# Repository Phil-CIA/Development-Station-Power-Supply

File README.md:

# Development-Station-Power-Supply

Integrated hardware and firmware repository for the development-station bench supply, its control electronics, front-panel display path, and supporting boards.

## What this repo actually contains

This is the active working repo for the full bench-supply platform, not just a single firmware target. It currently includes:

- ESP32 control firmware
- DSP regulator board design
- DSP regulator HAT / measurement-control board design
- original front-panel display board files
- USB hub board files and next-iter reference cleanup
- bring-up notes, pin maps, and display evaluation references

## Current direction (2026-08-14)

The project has shifted to a bring-up-first path.

**Recent progress:**
- Completed design simplification: migrated from adjustable 3-channel architecture to single +5V_Boot rail
- Connector contract verification passing (10 signal mappings validated across regulator↔HAT interface)
- Both RegulatorRevB and HAT-RevB boards electrically verified and ready for order prep

Current plan:
1. Use the hardware already built as the learning and validation baseline
2. Keep Rev-B bench work in proven bypass states while Rev-C electrical issues are closed
3. Complete Rev-C regulator and HAT design validation before PCB fabrication release
4. Continue front-panel work inside this repo
5. Evaluate two display paths in parallel:
   - the existing custom front-panel hardware already designed
   - the Elecrow CrowPanel Advance 4.3 inch HMI display
6. Avoid any new display redesign until bench results show it is needed

Current power-hardware status:

- The 3.3V regulator selector redesign is bench-proven in normal remote-sense operation; fallback and 5V TLV9352 checks remain open.
- The Rev-B HAT current-range switch remains bypassed pending MOSFET pinout and Vgs validation.
- HAT Rev-C implements four-channel differential OCP with dual INA2180A2 amplifiers and dual TLV1702 comparators.
- HAT Rev-C's 2026-08-14 clean ERC is superseded: a 2026-09-21 check found 82 ERC violations and 161 DRC violations plus 129 unconnected items (see RB-012). RB-012 remains a PCB release gate for Kelvin routing, bypassing, thresholds, hysteresis, footprints, and final DRC/connectivity validation.
- **Rev-D HAT is a hardware-first deliverable:** bare STM32F405RG LQFP64 plus the actual Teyleten Robot ESP32-C3 SuperMini are selected. The October 15 decisions in [#126](https://github.com/Phil-CIA/Development-Station-Power-Supply/issues/126) select native F405 USB CDC replacing CH340, a separate custom F405 loader over UART4 (PC10 TX to C3 GPIO0 RX; PC11 RX from GPIO1 TX), and independent ST-Link recovery. They supersede the October 13-14 USB-deferred/bare-MINI-1U proposals. The user's manually maintained `My_Edits` schematic must be preserved and reviewed; this worktree does not contain it and the repository's partial starter is not a substitute. Firmware pin alignment, electrical/footprint qualification, PCB/DRC, and bench validation remain open under #126; existing-indicator policy is [#125](https://github.com/Phil-CIA/Development-Station-Power-Supply/issues/125). See `docs/HAT_CONTROLLER_EVALUATION.md` for the reconciliation and historical review boundary. No fabrication or hardware validation is claimed.
- See `docs/DEV_STATION_HANDOFF_2026-08-14.md` for the active restart state.

**Immediate firmware priority (2026-10-24):** The next controller work is the
Rev-D STM32F405 transition. Do not spend bench time validating the compact F103
profile or continue optimizing F103 flash usage for future features. The F405
build already enables the full bring-up command set; its existing build is not
evidence of hardware compatibility or bench validation. Reconcile firmware
against the actual Rev-D hardware and re-verify behavior when that hardware is
available. See `docs/FIRMWARE_DEVELOPMENT_PLAN.md` and issue #126.

## Hardware scope in this repo

- External supply 12V feeds the regulator and HAT control stack
- Regulator board generates the main rails (+5V, +3.3V primary; +12V intermediate)
- HAT board handles measurement, feedback, and control behavior
- Front-panel display path is now treated as a system integration problem, not a redesign-first task
- USB hub files are retained as reference and redesign starting point where needed

## Hardware board status

**DSP-Regulator-RevB:** Ready for order
- ERC: 0 electrical errors (8 library warnings, non-critical)
- Connector contract: Verified against HAT-RevB (all 10 required signal mappings present)
- Latest netlist export: 2026-06-11 01:43:33

**DSP-Regulator-HAT-RevB:** Ready for order
- ERC: Clean (0 errors, 0 warnings)
- Connector contract: Verified with Regulator-RevB (all 10 required signal mappings present)
- Latest netlist export: 2026-06-11 01:10:51
- Design: Single +5V_Boot rail (simplified from adjustable 3-channel architecture)

These Rev-B files remain the built/bench baseline. Active redesign work now lives in the corresponding Rev-C project folders; do not release Rev-C fabrication outputs until its tracker gates are closed.

## Firmware status

Current firmware work in this repo includes:

- logical rail telemetry mapping
- automatic range selection support
- per-rail calibration and persistent configuration storage
- current-limit operating modes
- TFT front-panel support hooks

The active [CrowPanel UI plan](docs/display-project/crowpanel-screens-tracker.md)
adapts FNIRSI DPS-150 / IPS3608 styling to fixed +5V/+3.3V rails with editable
current limits and shared output control. It includes the issue/PR sequence
and VS Code Copilot session prompts; definitive CV/CC indication remains
gated on hardware validation.

## Current bench priorities

- Complete DRC checks and generate fabrication outputs for RegulatorRevB and HAT-RevB
- Place orders for both boards
- Safe first power-up and validation of the new boards
- Confirm regulator and HAT behavior on the bench
- Resume front-panel display bring-up
- Map the existing front-panel connector to the smart-display interface as needed

## Useful project references

- docs/SYSTEM_DEVELOPMENT_WORKFLOW.md — branch/PR workflow now in effect
- docs/FIRMWARE_DEVELOPMENT_PLAN.md — firmware feature inventory and milestone/branch plan
- docs/FAN_CONTROL_DEFINITION.md — issue #28 enclosure fan-control behavior spec (draft; tach path pending #29)
- docs/display-project/README.md
- docs/GPIO_PINOUT.md
- docs/USB_HUB_CHANGE_TRACKER.md
- docs/datasheets/README.md — local datasheet library; search with `python scripts/datasheet.py find <part>` before fetching

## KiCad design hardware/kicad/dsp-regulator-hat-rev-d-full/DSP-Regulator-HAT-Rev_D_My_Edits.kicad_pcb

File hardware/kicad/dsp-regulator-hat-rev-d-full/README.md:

# DSP Regulator HAT Rev-D Full - Selected-source integration

**Status: partial integration, not a complete full-HAT schematic.** The
editable HAT sheet was rebuilt on 2026-10-10 from the user's explicitly
selected Rev-C schematic. The design is not a fabrication release or a
bench-validated hardware identity; there is no PCB or PCB DRC result.

## Open and edit this project

- `DSP-Regulator-HAT-RevD-Full.kicad_pro` - project setup
- `DSP-Regulator-HAT-RevD-Full.kicad_sch` - root schematic
- `MCU.kicad_sch` - local hierarchical F405 support sheet
- `HAT.kicad_sch` - HAT circuits rebuilt from the selected Rev-C source
- `build_kicad/` - gitignored KiCad reports and exports

Open the `.kicad_pro` in KiCad 10.0.5. The root, MCU and HAT pages are
hierarchical pages 1, 2 and 3. The existing root schematic and MCU sheet were
left byte-identical. The reviewed support-only project in
`../dsp-regulator-hat-rev-d/` and the Rev-C projects remain separate and
unchanged.

## Selected HAT source

The user selected this exact file as the Rev-D HAT reuse baseline (the
2026-09-21 file):

`C:\Users\forch\OneDrive\JLCPCB files\Development station supply\Regulator Hat\REV C\KiCad Files\DSP-Regulator-HAT-RevC.kicad_sch`

Its SHA-256 is
`34EB41BA12237268CF8E8C640CFA2B76A4710CFF8DE99C9E988C9717D22872B3`.
A fresh KiCad CLI 10.0.5 netlist export contains **57 components and 83
nets**. This is a design-source selection only; it does not establish that
the schematic matches the supplied 2026-08-28 production PCB/Gerbers or any
physical board.

The earlier PR #112 pass used the repository Rev-C schematic (64 components,
105 nets). That source choice and its 0-error / 80-warning ERC result are
superseded and are not current validation evidence.

## HAT rebuild and interface mapping

The rebuilt HAT retains 55 of the selected source's 57 components. The old
Blue Pill U11 and ESP32-C3 development board U2, their no-connects, and
controller-only dangling labels/stubs were removed. No bare C3 module was
added. HAT references R1, R2 and R3 were renamed to R20, R21 and R22 because
the original references collide with the unchanged MCU sheet; their source
values and footprints are unchanged.

Existing F405 global labels were inspected before mapping. The supported
source paths are:

| F405 global interface | F405 pins | Selected-source HAT endpoints |
|---|---|---|
| `SPI_SCK`, `SPI_MISO`, `SPI_MOSI`, `Memory_CS` | PA5, PA6, PA7, PA8 | U12 W25Q128 |
| `UART1_TX`, `UART1_RX` | PB6, PB7 | U16 CH340C |
| `DISP_UART_TX`, `DISP_UART_RX` | PB10, PB11 | R77/R79 and J9 UDI |
| `I²C SCL_0`, `I²C SDA_0` | PB8, PB9 | J10 and U13 AHT20 |
| `FAN_PWM` | PB5 | R63/Q9 fan circuit; all source PB5 labels were normalized to this F405 global name without changing connector pin connectivity |
| `SWDIO`, `SWCLK` | PA13, PA14 | J17 and TP7/TP8 |

Source interface label changes are limited to `SPI SCK` -> `SPI_SCK`,
`SWDCLK` -> `SWCLK`, and `PB5` -> `FAN_PWM`; the source `+3.3V Boot` rail
labels were joined to the MCU's `+3V3` domain. The source J12 connector pin
mapping and all retained source-component pin connectivity remain unchanged.
The legacy WS2812B D12 DIN is grounded because its old controller is removed
and it is not the frozen low-current F405 LED circuit. CH340C CTS/RTS are
explicitly no-connected because the F405 contract uses TX/RX only.

The fan circuit is retained exactly from the selected schematic: J7 is a
3-pin connector; JP1 selects the J7/D11 supply path between `+5V_Boot` and
`+12V`; J7.1 is on the Q9-switched D11 path; J7.3 is a `Fan_Tach` endpoint
pulled up through source R3 (renumbered R22, 10 kΩ), with no F405 tach input.
Source R64 remains 100 kΩ. No fan polarity, supply, connector, resistor value
or population change was made to match the repository copy or frozen pin
target. The fan remains unbench-tested.

## Explicitly absent / unresolved

- The selected source has no ISET signal destinations at J12; its J12 pins
  remain GND, `+5V_Boot`, `+3.3V Boot`, `+12V`, GND, GND. F405 PA0/PA1 have
  their existing local bias circuitry but are not connected to invented HAT
  endpoints.
- The selected source has no shift register or AW9523. PA4/PC4/PC13 and the
  corresponding functions remain unintegrated; no endpoints were imported
  from the repository-only schematic or inferred from PCB content.
- MCU J4 remains a logical C3 interface on the support sheet, not a bare
  ESP32-C3-MINI-1U module implementation. The selected-source HAT UART labels
  are not connected to J4. C3 module power/straps/recovery/RF remain later
  work.
- The fan's source 100 kΩ R64 does not meet the frozen 10 kΩ fan-gate target;
  it was not changed. The pin-contract and safe-state review is still open.
- Remaining isolated legacy connector labels and missing custom library
  definitions are visible ERC warnings, not integrated functions.

## Validation

KiCad CLI 10.0.5 exports the three-sheet project as **95 components and 107
nets**. The comparison against the selected source confirms all 55 retained
source component values/footprints and all **1,056 pairwise source-component
pin connections** are unchanged, except D12 DIN, which is intentionally
grounded. Reference mapping is R1/R2/R3 -> R20/R21/R22. The expected SPI
flash, CH340, UDI, I2C, fan-control and SWD data/clock interfaces were checked
against the actual F405 global labels and netlist. J12 connector pins and the
source fan topology were checked separately.

Full-severity ERC reports **0 errors / 64 warnings**: 28 footprint-library,
28 symbol-library, 3 symbol/library mismatch and 5 isolated-pin-label
warnings. The report is generated with `--severity-all`; no ERC exclusions
were added. The warnings expose missing local library tables and unresolved
single-ended legacy connector labels. ERC/netlist checks are not PCB DRC,
electrical qualification, physical-board correlation, fabrication approval
or bench validation.

The exact source file, the full-project root/MCU files, the support-only
project, both repository Rev-C projects and the external production folder
were hash-checked; only the intended full-project HAT sheet changed among
those KiCad design files. See
[`HAT_REVD_PIN_AND_SUPPORT_CONTRACT.md`](../../../docs/HAT_REVD_PIN_AND_SUPPORT_CONTRACT.md)
for current boundaries and remaining release gates.

Re-run from the repository root in PowerShell:

```powershell
$project = "hardware\kicad\dsp-regulator-hat-rev-d-full"
$kicad = "$env:LOCALAPPDATA\Programs\KiCad\10.0\bin\kicad-cli.exe"
& $kicad sch erc "$project\DSP-Regulator-HAT-RevD-Full.kicad_sch" `
  --output "$project\build_kicad\ERC.rpt" --format report --severity-all
& $kicad sch export netlist "$project\DSP-Regulator-HAT-RevD-Full.kicad_sch" `
  --output "$project\build_kicad\DSP-Regulator-HAT-RevD-Full.net" `
  --format kicadsexpr
```

## SuperMini review closeout (user-accepted baseline)

- User accepted directly soldered through-hole header mounting for
  `SuperMini_Review:Teyleten_ESP32_C3_SuperMini` with the saved geometry:
  2.54mm pitch, 15.00mm row spacing, aligned rows, 1.7mm copper / 1.0mm
  drill, existing numbering, and USB at negative Y.
- Saved footprint text was audited and KiCad opening was user-confirmed.
- Physical hole fit, body/USB envelope, installed height, and antenna
  clearance were not verified in this review and are retained as
  implementation caveats (not blockers for this user-requested closeout).
- U2 assignment and PCB integration were not performed.
- Project-local library and footprint paths:
  - `hardware/kicad/dsp-regulator-hat-rev-d-full/fp-lib-table`
  - `hardware/kicad/dsp-regulator-hat-rev-d-full/SuperMini_Review.pretty/Teyleten_ESP32_C3_SuperMini.kicad_mod`

## Rev-D source preservation status (2026-10-24 user-confirmed)

- Confirmed Rev-D source set in this workspace:
  - `DSP-Regulator-HAT-Rev_D_My_Edits.kicad_sch`
  - `DSP-Regulator-HAT-Rev_D_My_Edits.kicad_pro`
  - `DSP-Regulator-HAT-Rev_D_My_Edits.kicad_pcb`
- SHA-256 (full):
  - `DSP-Regulator-HAT-Rev_D_My_Edits.kicad_sch`
    `56DBB1829EC3D60BC174B423BB3C076FEBDE61CBA844A3334B06E9B805610F86`
  - `DSP-Regulator-HAT-Rev_D_My_Edits.kicad_pro`
    `70C6AB58C39FFBC618B4C45C720BD51EEC6F3F04F0216B5DFA340010E44D0D51`
  - `DSP-Regulator-HAT-Rev_D_My_Edits.kicad_pcb`
    `8F7872B7946E3F1403190E5051BBDE5EB1976761201A710C185F5A749642770A`
- Historical copies only (not current source authority): `.history/`, `_restore_backup_*`,
  `../recovery-snapshots/`, and `../rev-d-source-staging/`.
- Current `DSP-Regulator-HAT-Rev_D_My_Edits.net`, `ERC.rpt`, and `DRC.rpt` files predate
  the current source timestamps and do not validate electrical correctness of this source set.

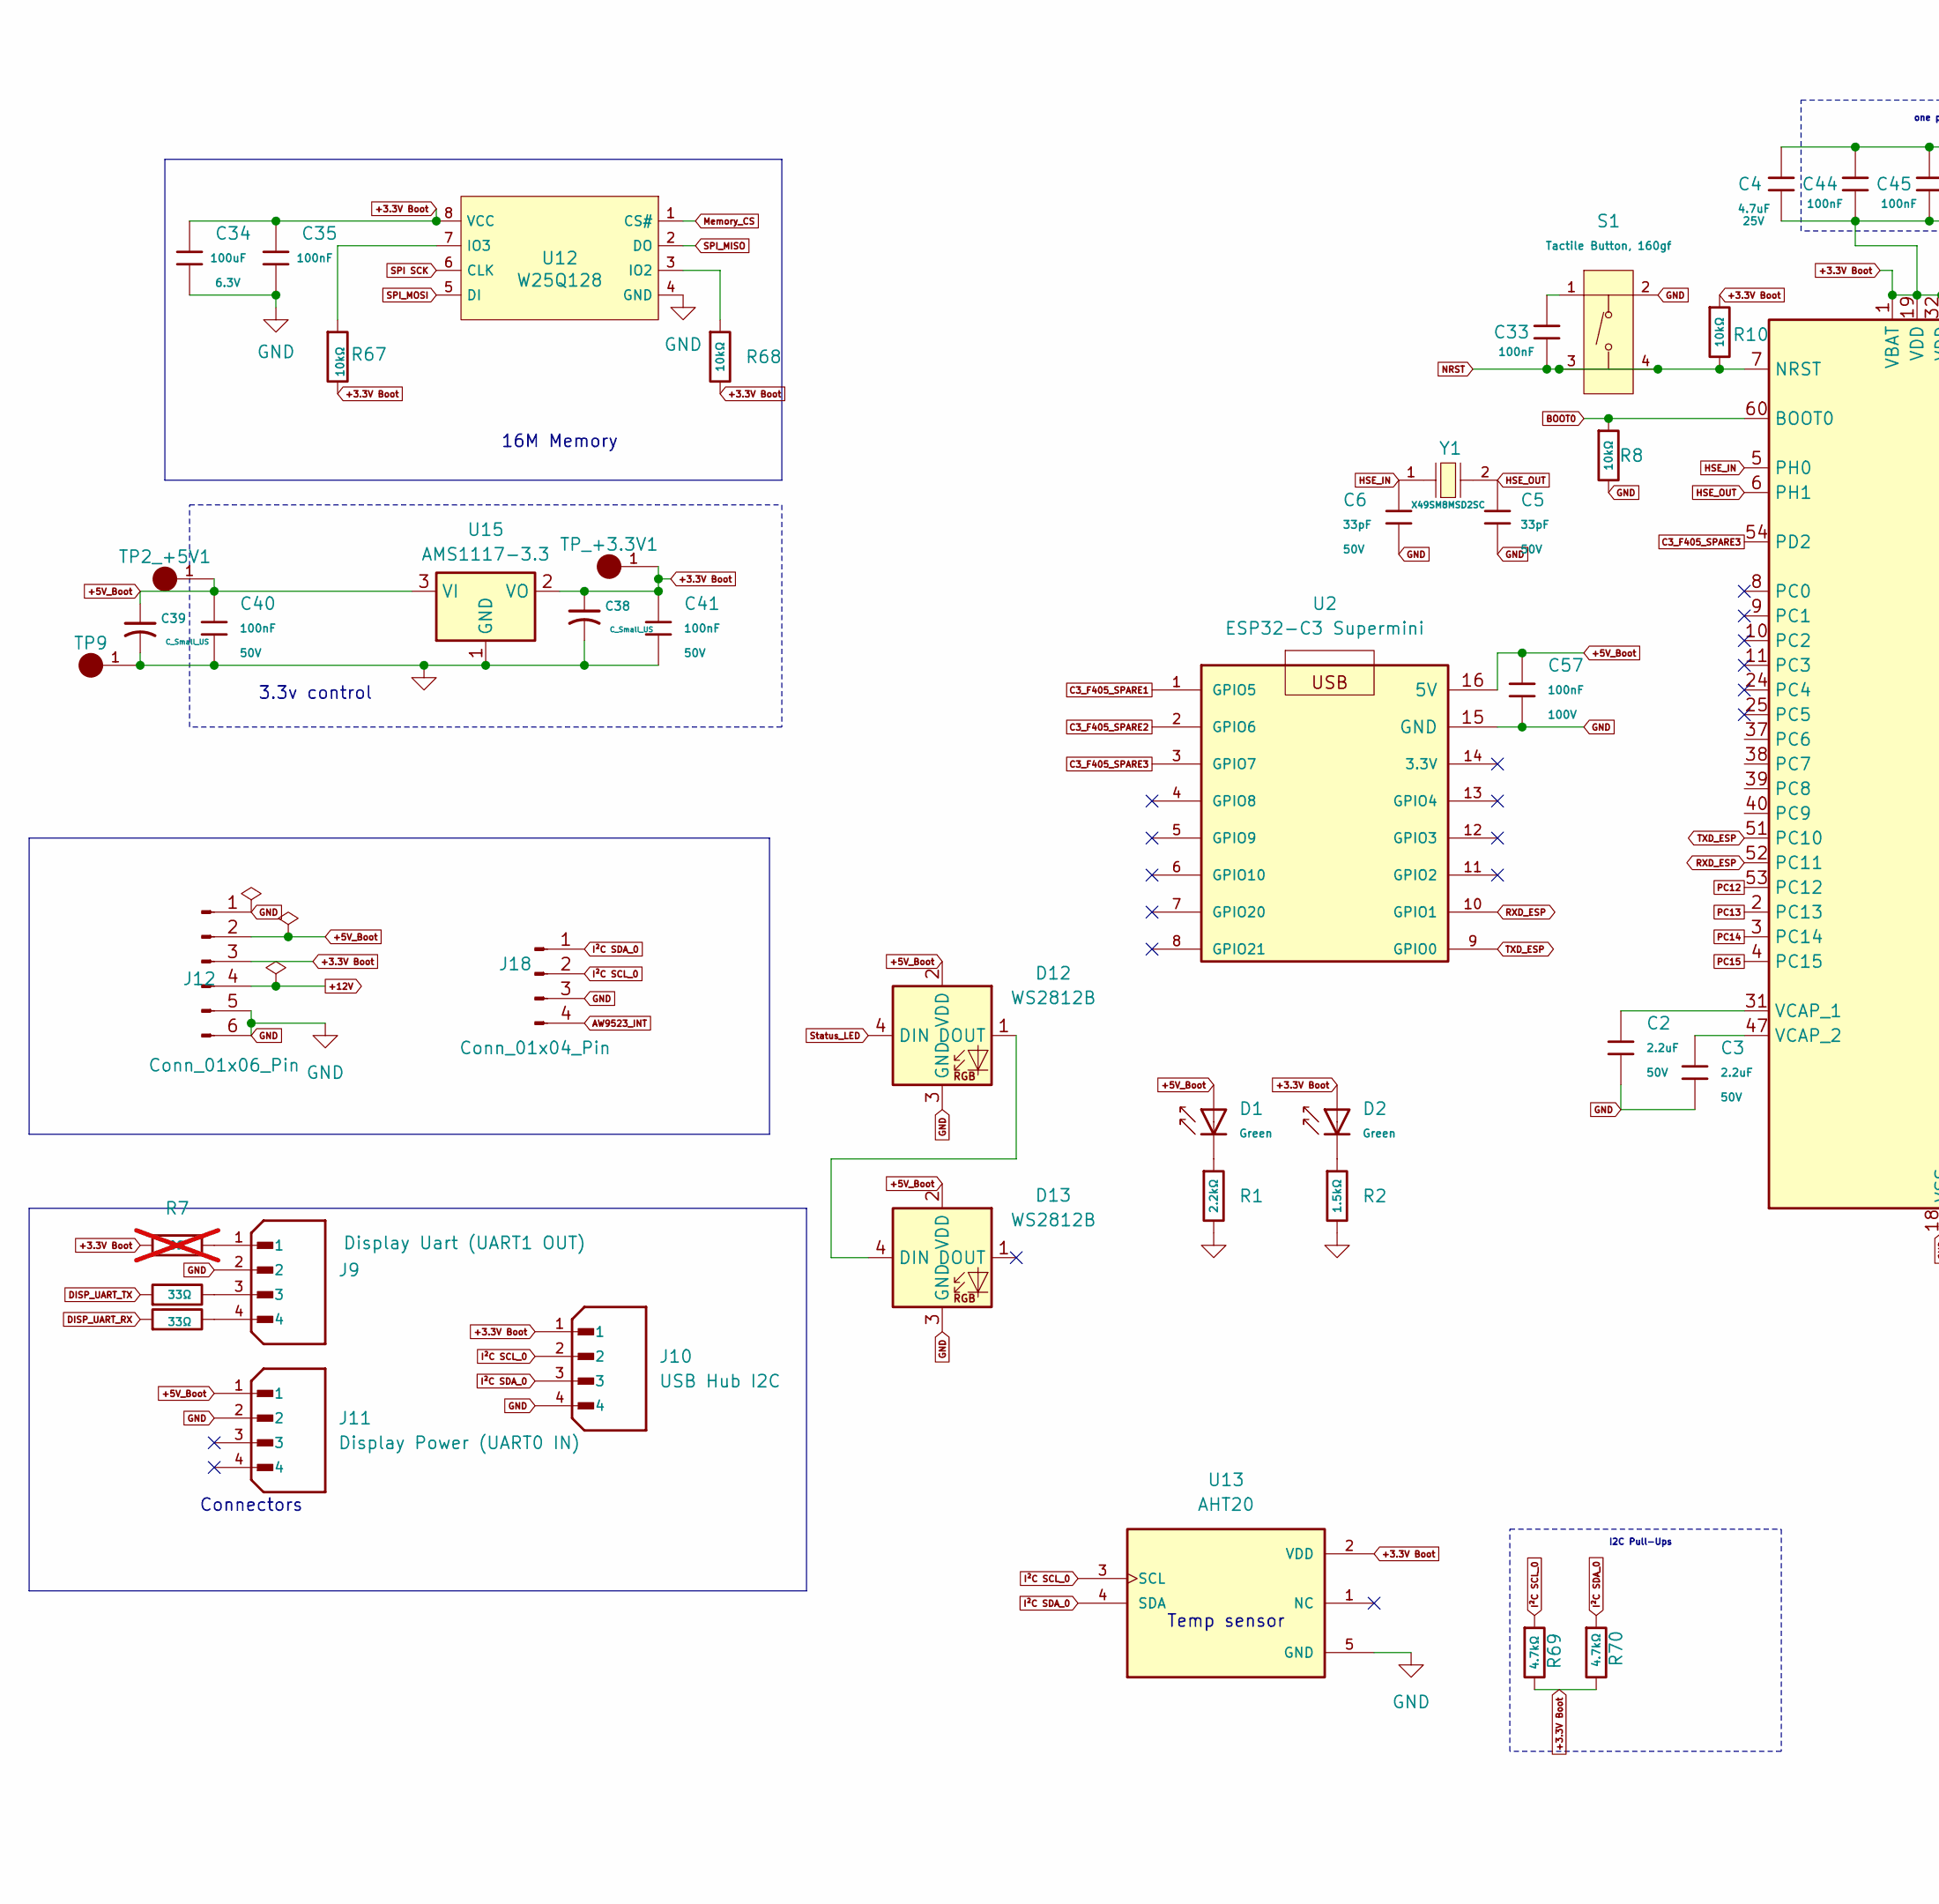
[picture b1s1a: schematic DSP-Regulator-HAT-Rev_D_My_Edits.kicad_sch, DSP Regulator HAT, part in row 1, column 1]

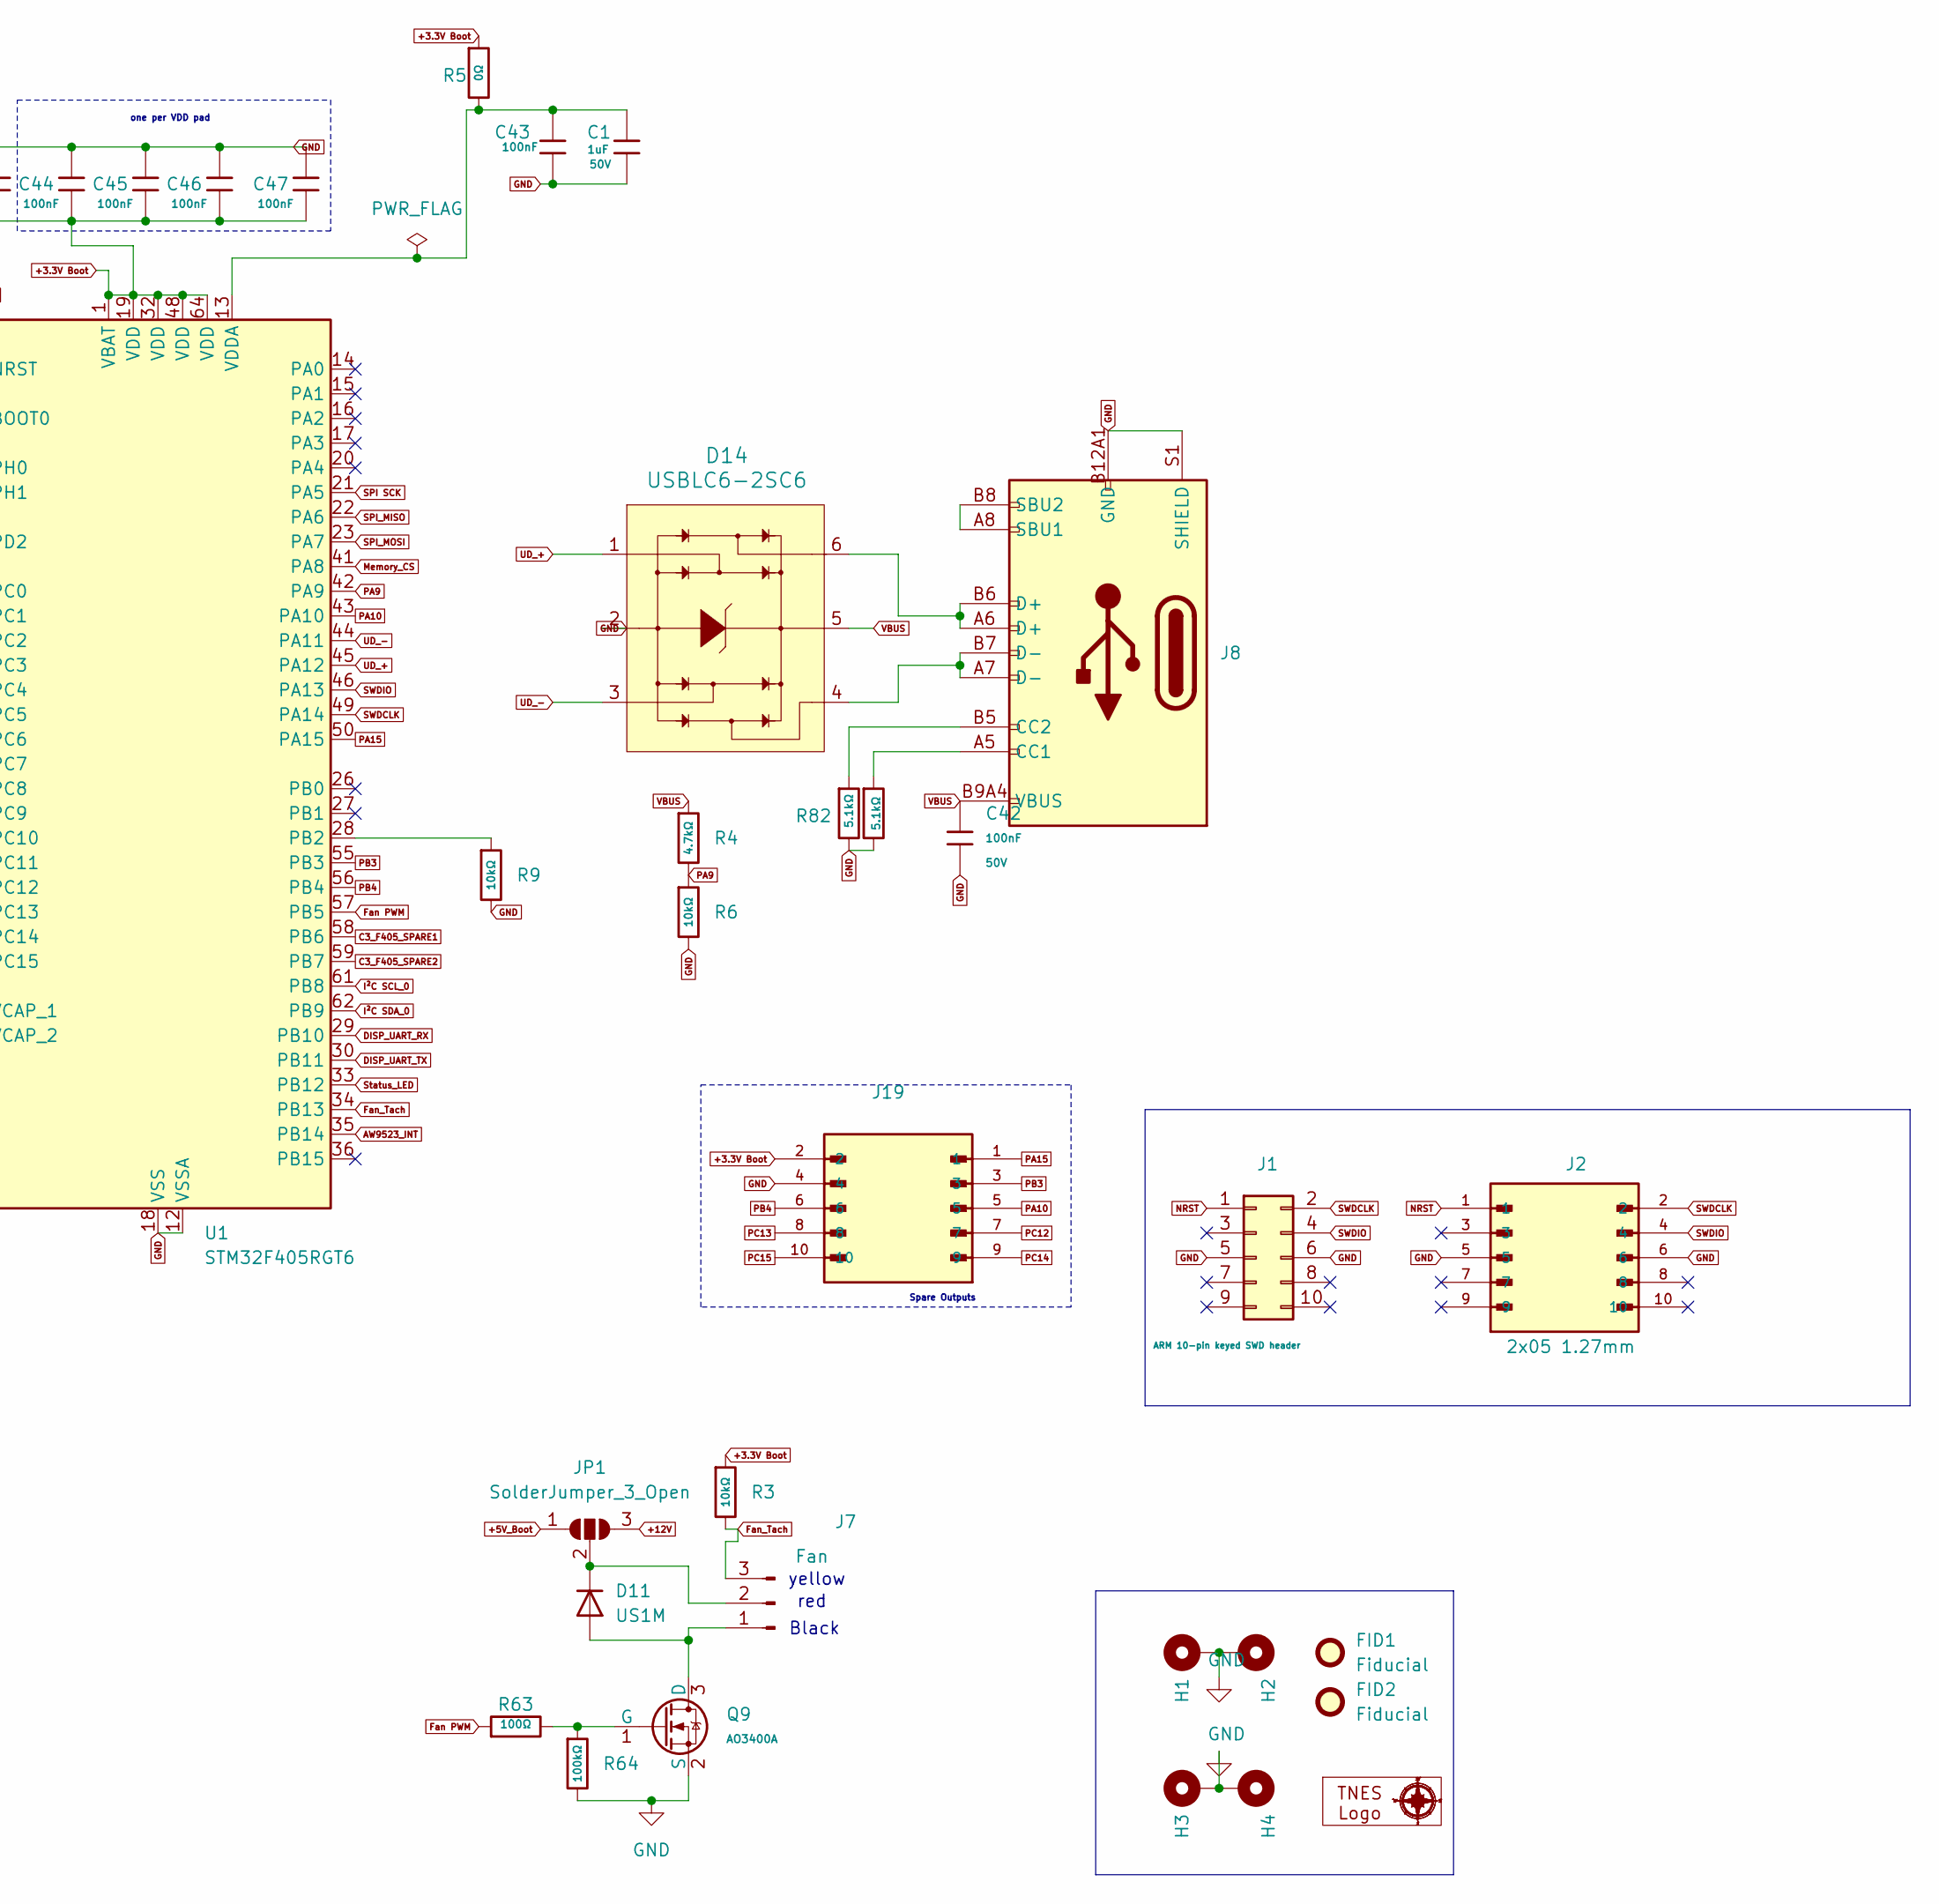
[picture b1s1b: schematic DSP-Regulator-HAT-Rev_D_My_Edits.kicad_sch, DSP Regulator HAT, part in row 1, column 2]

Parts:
5mm1: 5mm LOGO
C1: 1uF; C_0805; Voltage Rated 50V; Tolerance ±10%; Part CL21B105KBFNNNE; LCSC C28323
C2, C3: 2.2uF; C_0805; Voltage Rated 50V; Tolerance ±10%; Part CL21A225KBQNNNE; LCSC C377773
C4: 4.7uF; C_0805; Voltage Rated 25V; Tolerance ±10%; Part CL21A475KAQNNNE; LCSC C1779
C5, C6: 33pF; C_0805; Voltage Rated 50V; Tolerance ±5%; Part CC0805JRNPO9BN330; LCSC C107115
C33, C35, C40, C41, C42, C43, C44, C45, C46, C47: 100nF; C_0805; Voltage Rated 50V; Tolerance ±10%; Part CC0805KRX7R9BB104; LCSC C49678
C34: 100uF; C_1206; Voltage Rated 6.3V; Tolerance ±20%; Part CL31A107MQHNNNE; LCSC C15008
C38, C39: C_Small_US; CP_Elec_10x10; Part JVE25V470M10X10; LCSC C48615124
C57: 100nF; C_0805; Voltage Rated 100V; Tolerance ±10%; Part CL21B104KCFNNNE; LCSC C28233
D1, D2: Green; D_0805; Part KT-0805G; LCSC C2297
D11: US1M; D_SMA; LCSC C81191
D12, D13: WS2812B; LED-SMD_4P-L1.6-W1.5_XL-1615RGBC-WS2812B; LCSC C5349954
D14: USBLC6-2SC6; SOT23-6L; MPN USBLC6-2SC6; Digi-Key_PN 497-5235-1-ND
FID1, FID2: Fiducial; Fiducial_0.75mm_Mask1.5mm
H1, H2, H3, H4: MountingHole_Pad; MountingHole_3.5mm_Pad_Via
J1: ARM 10-pin keyed SWD header; IDC-Header_2x05_P2.54mm_Vertical
J2: 2x05 1.27mm; PinHeader_2x5_P1.27mm; PARTREV S
J7: Fan; PinHeader_1x03_P2.54mm_Vertical; LCSC C29275
J8: Connector, USB-TYPE-C-16P; TYPE-C-SMD_HX-TYPE-C-16PIN; LCSC C2927039
J9: Display Uart (UART1 OUT); JST_B4B-XH-A; PARTREV 7/4/21; LCSC C144395
J10: USB Hub I2C; JST_B4B-XH-A; PARTREV 7/4/21; LCSC C144395
J11: Display Power (UART0 IN); JST_B4B-XH-A; PARTREV 7/4/21; LCSC C144395
J12: Conn_01x06_Pin; PinHeader_1x06_P2.54mm_Vertical; LCSC C492414
J18: Conn_01x04_Pin; PinHeader_1x04_P2.54mm_Vertical; LCSC C492412
J19: 20021121-00010C4LF; PinHeader_2x5_P1.27mm; PARTREV S; LCSC C41376037
JP1: SolderJumper_3_Open; SolderJumper-3_P1.3mm_Open_RoundedPad1.0x1.5mm
Q9: AO3400A; Q_SOT-23; Part AO3400A; LCSC C20917
R1: 2.2kΩ; R_0805; Overload Voltage (Max) 150V; Tolerance ±1%; Part 0805W8F2201T5E; LCSC C17520
R2: 1.5kΩ; R_0805; Overload Voltage (Max) 150V; Tolerance ±1%; Part 0805W8F1501T5E; LCSC C4310
R3, R6, R8, R9, R10, R67, R68: 10kΩ; R_0805; Overload Voltage (Max) 150V; Tolerance ±1%; Part 0805W8F1002T5E; LCSC C17414
R4, R69, R70: 4.7kΩ; R_0805; Overload Voltage (Max) 150V; Tolerance ±1%; Part 0805W8F4701T5E; LCSC C17673
R5: 0Ω; R_0805; Overload Voltage (Max) 150V; Tolerance ±1%; Part 0805W8F0000T5E; LCSC C17477
R7: 0Ω; R_0805; Overload Voltage (Max) 150V; Tolerance ±1%; Part 0805W8F0000T5E; LCSC C17477; not fitted
R63: 100Ω; R_0805; Overload Voltage (Max) 150V; Tolerance ±1%; Part 0805W8F1000T5E; LCSC Part C105588
R64: 100kΩ; R_0805; Overload Voltage (Max) 150V; Tolerance ±1%; Part 0805W8F1003T5E; LCSC C149504
R77, R79: 33Ω; R_0805; Overload Voltage (Max) 150V; Tolerance ±1%; Part 0805W8F330JT5E; LCSC C17634
R82, R83: 5.1kΩ; R_0805; Overload Voltage (Max) 150V; Tolerance ±1%; Part 0805W8F5101T5E; LCSC C27834
S1: Tactile Button, 160gf; SW-SMD_4P-L5.1-W5.1-P3.70-LS6.5-TL-2; Voltage Rating (Dc) 12V; Part TS-1187A-B-A-B; LCSC C318884
TP2_+5V1, TP9: 5015; KEYSTONE_5015; PARTREV F; LCSC C5199798
TP_+3.3V1: 5015; KEYSTONE_5015; PARTREV F; LCSC C5199798
U1: STM32F405RGT6; LQFP-64_10x10mm_P0.5mm
U2: ESP32-C3 Supermini; Teyleten_ESP32_C3_SuperMini; PARTREV 23/05/2022
U12: W25Q128; SOIC-8_L5.3-W5.3-P1.27-LS8.0-BL; Part W25Q128JVSIQ; LCSC C97521
U13: AHT20; Humidity sensor; PARTREV V1.0; LCSC Part C2757850
U15: AMS1117-3.3; SOT-223-3_TabPin2; LCSC C6186
Y1: X49SM8MSD2SC; CRYSTAL-SMD_L11.5-W4.8-LS12.7; Frequency Tolerance ±20ppm; Part X49SM8MSD2SC; LCSC C12674

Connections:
+3.3V Boot: C4.2, C34.1, C35.1, C38.1, C41.1, C44.2, C45.2, C46.2, C47.2, D2.2, J10.1, J12.3, J19.2, R3.1, R5.1, R7.1, R10.1, R67.2, R68.2, R69.2, R70.2, TP_+3.3V1.1, U1.1 (VBAT), U1.19 (VDD), U1.32 (VDD), U1.48 (VDD), U1.64 (VDD), U12.8 (VCC), U13.2 (VDD), U15.2 (VO)
+5V_Boot: C39.1, C40.1, C57.1, D1.2, D12.2 (VDD), D13.2 (VDD), J11.1, J12.2, JP1.1 (A), TP2_+5V1.1, U2.16 (5V), U15.3 (VI)
+12V: J12.4, JP1.3 (B)
AW9523_INT: J18.4, U1.35 (PB14)
BOOT0: R8.1, U1.60 (BOOT0)
C3_F405_SPARE1: U1.58 (PB6), U2.1 (GPIO5)
C3_F405_SPARE2: U1.59 (PB7), U2.2 (GPIO6)
C3_F405_SPARE3: U1.54 (PD2), U2.3 (GPIO7)
DISP_UART_RX: R79.1, U1.29 (PB10)
DISP_UART_TX: R77.1, U1.30 (PB11)
Fan PWM: R63.1, U1.57 (PB5)
Fan_Tach: J7.3, R3.2, U1.34 (PB13)
GND: C1.1, C2.2, C3.2, C4.1, C5.2, C6.2, C34.2, C35.2, C38.2, C39.2, C40.2, C41.2, C42.2, C43.2, C44.1, C45.1, C46.1, C47.1, C57.2, D12.3 (GND), D13.3 (GND), D14.2, H1.1 (1_1), H2.1 (1_1), H3.1 (1_1), H4.1 (1_1), J1.5, J1.6, J2.5, J2.6, J8.A12B1 (GND), J8.B12A1 (GND), J8.S1 (SHIELD), J9.2, J10.4, J11.2, J12.1, J12.5, J12.6, J18.3, J19.4, Q9.2 (S), R1.2, R2.2, R6.2, R8.2, R9.2, R64.2, R82.2, R83.2, S1.2 (B), TP9.1, U1.12 (VSSA), U1.18 (VSS), U1.63 (VSS), U2.15 (GND), U12.4 (GND), U13.5 (GND), U15.1 (GND)
HSE_IN: C6.1, U1.5 (PH0), Y1.1
HSE_OUT: C5.1, U1.6 (PH1), Y1.2
I²C SCL_0: J10.2, J18.2, R69.1, U1.61 (PB8), U13.3 (SCL)
I²C SDA_0: J10.3, J18.1, R70.1, U1.62 (PB9), U13.4 (SDA)
Memory_CS: U1.41 (PA8), U12.1 (CS#)
NRST: C33.2, J1.1, J2.1, R10.2, S1.3 (C), S1.4 (D), U1.7 (NRST)
unnamed: D1.1, R1.1
unnamed: D2.1, R2.1
unnamed: D11.2 (A), J7.1, Q9.3 (D)
unnamed: D11.1 (K), J7.2, JP1.2 (C)
unnamed: D12.1 (DOUT), D13.4 (DIN)
unnamed: D14.4, J8.A7 (D-), J8.B7 (D-)
unnamed: D14.6, J8.A6 (D+), J8.B6 (D+)
unnamed: J8.A5 (CC1), R83.1
unnamed: J8.B5 (CC2), R82.1
unnamed: J8.A8 (SBU1), J8.B8 (SBU2)
unnamed: J9.1, R7.2
unnamed: J9.3, R77.2
unnamed: J9.4, R79.2
unnamed: Q9.1 (G), R63.2, R64.1
unnamed: C33.1, S1.1 (A)
unnamed: R9.1, U1.28 (PB2)
unnamed: C2.1, U1.31 (VCAP_1)
unnamed: C3.1, U1.47 (VCAP_2)
unnamed: C1.2, C43.1, R5.2, U1.13 (VDDA)
unnamed: R68.1, U12.3 (IO2)
unnamed: R67.1, U12.7 (IO3)
PA9: R4.2, R6.1, U1.42 (PA9)
PA10: J19.5, U1.43 (PA10)
PA15: J19.1, U1.50 (PA15)
PB3: J19.3, U1.55 (PB3)
PB4: J19.6, U1.56 (PB4)
PC12: J19.7, U1.53 (PC12)
PC13: J19.8, U1.2 (PC13)
PC14: J19.9, U1.3 (PC14)
PC15: J19.10, U1.4 (PC15)
RXD_ESP: U1.52 (PC11), U2.10 (GPIO1)
SPI SCK: U1.21 (PA5), U12.6 (CLK)
SPI_MISO: U1.22 (PA6), U12.2 (DO)
SPI_MOSI: U1.23 (PA7), U12.5 (DI)
SWDCLK: J1.2, J2.2, U1.49 (PA14)
SWDIO: J1.4, J2.4, U1.46 (PA13)
Status_LED: D12.4 (DIN), U1.33 (PB12)
TXD_ESP: U1.51 (PC10), U2.9 (GPIO0)
UD_+: D14.1, U1.45 (PA12)
UD_-: D14.3, U1.44 (PA11)
VBUS: C42.1, D14.5, J8.A9B4 (VBUS), J8.B9A4 (VBUS), R4.1

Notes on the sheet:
Connectors
I2C Pull-Ups
Temp sensor
red
3.3v control
16M Memory
Spare Outputs
Black
yellow
one per VDD pad

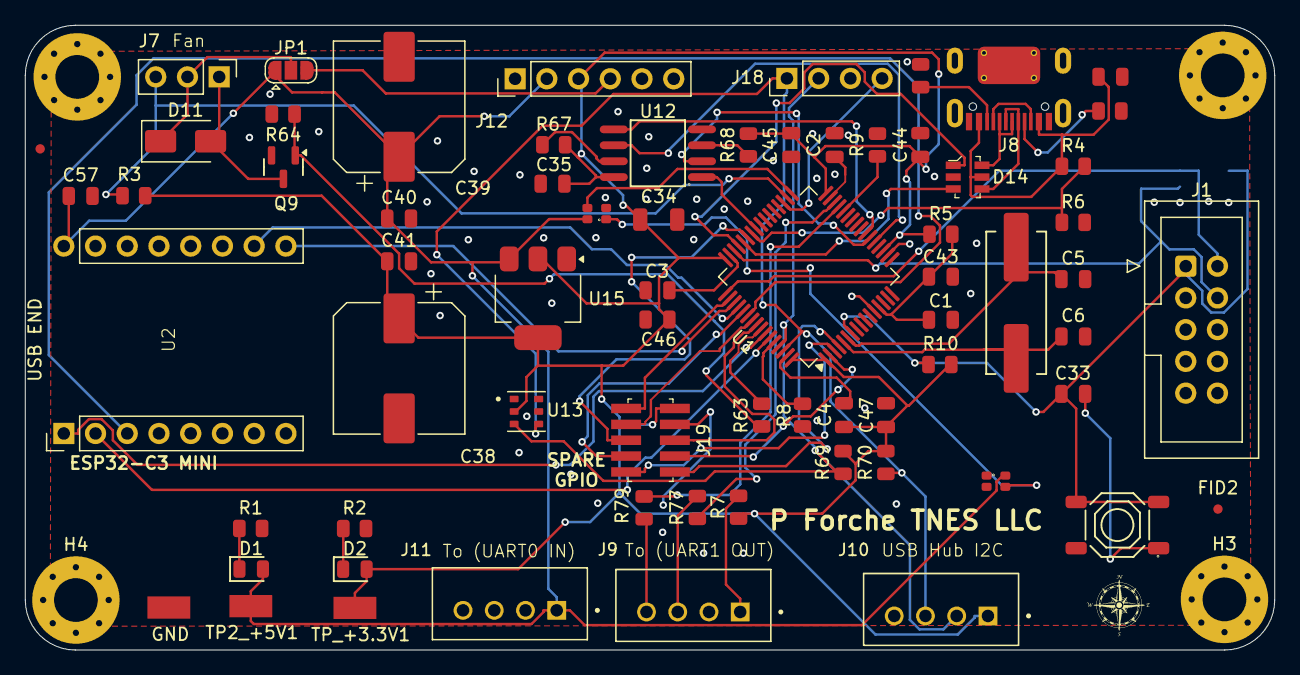
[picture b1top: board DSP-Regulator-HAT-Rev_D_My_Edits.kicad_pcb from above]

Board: 2 copper layers, 100.0 x 50.0 mm, 75 parts (1 on the bottom side), 60 nets.

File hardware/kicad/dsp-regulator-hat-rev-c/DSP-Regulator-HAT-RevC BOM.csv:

"Reference","Qty","Value","LCSC","MPN","Manufacturer","Part","MF"
"5mm1","1","","","","","",""
"C32,C36,C37,C40,C41,C42,C57","7","100nF","C28233,C49678","","Samsung Electro-Mechanics,YAGEO","CC0805KRX7R9BB104,CL21B104KCFNNNE",""
"C34","1","100uF","C15008","","Samsung Electro-Mechanics","CL31A107MQHNNNE",""
"C35","1","100nF","C49678","","YAGEO","CC0805KRX7R9BB104",""
"C38,C39","2","C_Small_US","C48615124","","","JVE25V470M10X10",""
"D1,D2","2","Green","C2297","","Hubei KENTO Elec","KT-0805G",""
"D11","1","US1M","C81191","","","",""
"D12","1","WS2812B","C5349954","","","",""
"D14","1","USBLC6-2SC6","C7519","USBLC6-2SC6","STMicroelectronics","",""
"J7","1","Fan","C29275","","","",""
"J8","1","Connector, USB-TYPE-C-16P","C2927039","","","",""
"J9","1","Display Uart","C144395","B4B-XH-A(LF)(SN)","JST","B4B-XH-A(LF)(SN)",""
"J10","1","USB Hub I2C","C144395","B4B-XH-A(LF)(SN)","JST","B4B-XH-A(LF)(SN)",""
"J12","1","Conn_01x06_Pin","C492414","PZ254R-11-06P","XFCN","PZ254R-11-06P",""
"J17","1","JTAG","C53207560","","","",""
"J18","1","Conn_01x04_Pin","C492412","PZ254R-11-04P","XFCN","PZ254R-11-04P",""
"J19","1","20021121-00010C4LF"," C41376037","","","",""
"Q9","1","AO3400A","C20917","","Alpha & Omega Semicon","AO3400A",""
"R1","1","470Ω","C17710","","UNI-ROYAL(Uniroyal Elec)","0805W8F4700T5E",""
"R2","1","150Ω","C17471","","UNI-ROYAL(Uniroyal Elec)","0805W8F1500T5E",""
"R3","1","10kΩ","C17414","","UNI-ROYAL(Uniroyal Elec)","0805W8F1002T5E",""
"R63","1","100Ω","C17408","","UNI-ROYAL(Uniroyal Elec)","0805W8F1000T5E",""
"R64","1","100kΩ","C149504","","UNI-ROYAL(Uniroyal Elec)","0805W8F1003T5E",""
"R67,R68","2","10kΩ","C17414","","UNI-ROYAL(Uniroyal Elec)","0805W8F1002T5E",""
"R69,R70","2","4.7kΩ","C17673","","UNI-ROYAL(Uniroyal Elec)","0805W8F4701T5E",""
"R77,R79","2","33Ω","C17634","","UNI-ROYAL(Uniroyal Elec)","0805W8F330JT5E",""
"R82,R83","2","5.1kΩ","C27834","","UNI-ROYAL(Uniroyal Elec)","0805W8F5101T5E",""
"TP2_+5V1,TP9,TP_+3.3V1","3","5015","C5199798","","","",""
"TP7,TP8","2","TestPoint_Small","","","","",""
"U2","1","ESP32-C3 Supermini","","","","","Teyleten Robot"
"U11","1","STM32_BLUE -","","","","",""
"U12","1","W25Q128","C97521","","Winbond Elec","W25Q128JVSIQ",""
"U13","1","AHT20","C2757850","","","","Asair"
"U15","1","AMS1117-3.3","C6186","","","",""
"U16","1","CH340C","C84681","CH340C","WCH","CH340C",""
